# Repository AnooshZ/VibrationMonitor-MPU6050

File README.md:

# 📈 Vibration Monitoring System | Arduino → STM32 Custom PCB

A real-time vibration monitoring system built around the **MPU6050 accelerometer**, originally developed using an Arduino UNO and Python, and subsequently redesigned around an **STM32F103 microcontroller on a custom-designed PCB**.

The project explores embedded systems, sensor interfacing, digital signal processing, PCB design, and hardware debugging.

The original Arduino prototype successfully demonstrated vibration detection, signal filtering, threshold-based LED indication, and real-time Python visualization. The STM32 redesign aims to improve sampling consistency, timing control, and overall system flexibility while providing practical experience developing and validating custom embedded hardware.

**Current Status: Custom PCB manufactured, assembled, powered, and successfully programmed. Hardware bring-up completed; STM32 firmware development in progress.**

---

## 🎯 Project Overview

The project began as an experiment in vibration analysis using an Arduino UNO and MPU6050 accelerometer.

The initial implementation acquired accelerometer measurements, processed vibration data, applied filtering, and communicated results to a Python application for real-time visualization and data logging.

Although the prototype worked, I encountered limitations involving sampling consistency, timing accuracy, and flexibility in controlling the underlying hardware.

To address these limitations, I redesigned the system around an STM32F103C8T6 microcontroller and developed my first custom PCB using KiCad.

A major objective throughout this redesign was to learn directly from technical documentation rather than relying heavily on tutorials. This involved studying component datasheets, application notes, and the STM32 reference manual to understand peripheral configuration, clock circuitry, power distribution, communication interfaces, and PCB layout.

---

## 🚀 Project Development Status

| Stage | Status |
|---|---|
| Arduino + MPU6050 prototype | ✅ Complete |
| Vibration detection and filtering | ✅ Complete on Arduino |
| Python visualization and CSV logging | ✅ Complete on Arduino |
| STM32 schematic design | ✅ Complete |
| Custom PCB layout and design-rule verification | ✅ Complete |
| PCB manufacturing and assembly | ✅ Complete |
| Power rail verification | ✅ Complete |
| SWD communication and MCU identification | ✅ Complete |
| STM32 programming and debugging | ✅ Complete |
| Bare-metal GPIO configuration and LED blinking | ✅ Complete |
| External MPU6050 integration | 🔄 Upcoming |
| STM32 I²C firmware | 🔄 Upcoming |
| STM32 vibration acquisition and processing | 🔄 Planned |
| STM32-to-Python communication | 🔄 Planned |
| Physical board demonstration videos | 🔄 Coming soon |

---

## 🧠 Original Arduino Prototype

The first version of the system was developed using an Arduino UNO, MPU6050 sensor module, and Python.

### Features

- Real-time vibration measurements using the MPU6050 three-axis accelerometer
- High-pass filtering to reduce unwanted low-frequency components
- RMS smoothing for more stable vibration measurements
- Threshold-based LED indication
- Serial communication between Arduino and Python
- Real-time plotting of vibration magnitude and RMS values
- Timestamped CSV logging for further analysis
- Initial experimentation with FFT-based vibration analysis

### Hardware

- Arduino UNO
- MPU6050 accelerometer module
- Breadboard and jumper wires
- LED with current-limiting resistor
- USB connection for serial communication

### Arduino Connections

| Arduino Pin | Connection |
|---|---|
| 5V | MPU6050 module VCC |
| GND | MPU6050 GND |
| A4 | MPU6050 SDA |
| A5 | MPU6050 SCL |
| D8 | LED output |

### Software

**Arduino:** Acquires acceleration measurements, performs vibration-related calculations, applies filtering, and activates the LED when the configured vibration threshold is exceeded.

**Python:** Receives serial measurements, plots vibration magnitude and RMS values in real time, and saves measurement data for later analysis.

### Original Prototype Demonstration

[Watch the Arduino vibration monitoring demo](Demo/VibrationsMonitorDemo.mp4)

The demonstration uses a massage gun to introduce controlled vibrations at different intensity levels.

At lower vibration levels, the LED remains off. At higher vibration levels, the measured vibration exceeds the threshold and activates the LED.

The Python visualization displays the corresponding changes in vibration magnitude and RMS measurements.

---

## 🔧 STM32 Custom PCB Redesign

The second iteration replaces the Arduino development board with a custom PCB designed around the **STM32F103C8T6 ARM Cortex-M3 microcontroller**.

This redesign provides greater control over the hardware and creates a foundation for implementing more consistent sampling, hardware timers, sensor communication, and embedded signal processing.

### Hardware Features

| Component / Interface | Purpose |
|---|---|
| STM32F103C8T6 | Main ARM Cortex-M3 microcontroller |
| TPS7A2033 LDO | Regulated 3.3V power supply |
| 8 MHz external crystal | External clock source |
| USB Micro-B connector | USB connectivity and power input |
| USB ESD protection | Protection for USB data lines |
| SWD header | Programming and hardware debugging |
| UART header | Serial communication and debugging |
| I²C header | External MPU6050 sensor connection |
| Analog supply filtering | Filtering for the MCU analog power domain |
| BOOT0 selection switch | Boot mode configuration |
| Reset circuitry | MCU reset control |
| Status LEDs | Power indication and firmware-controlled output |

### Power Distribution

The PCB uses a dedicated 3.3V low-dropout regulator to supply the STM32 and associated circuitry.

The design includes local decoupling capacitors near the microcontroller power pins, bulk capacitance for supply stability, and filtering for the analog supply domain.

### Clock Circuitry

An 8 MHz external crystal and its supporting capacitors are included to provide an external clock option.

The STM32 can also operate using its internal oscillator, allowing firmware development and initial bring-up without requiring the external crystal to be configured.

### Programming and Debugging

A dedicated SWD header exposes the STM32 programming and debugging signals.

Using an ST-Link programmer and STM32CubeIDE, the microcontroller can be programmed, halted, inspected, and debugged directly on the custom PCB.

### Sensor Interface

The PCB includes an I²C header for connecting an external MPU6050 module.

This allows the sensor interface to be developed and tested independently before integrating vibration processing into the STM32 firmware.

---

## 🛠️ PCB Design and Manufacturing

The schematic and PCB layout were developed in **KiCad**.

The design process involved:

- Studying STM32 datasheets and reference documentation
- Selecting components and verifying footprints
- Designing the power distribution and decoupling networks
- Implementing clock, reset, boot, USB, and debugging circuitry
- Routing a two-layer PCB
- Considering return paths, trace routing, and placement of decoupling components
- Running electrical rule checks (ERC) and design rule checks (DRC)
- Preparing manufacturing files and a bill of materials
- Ordering and assembling the physical PCB

The boards were manufactured through **JLCPCB**, with additional manual soldering and hardware bring-up performed after delivery.

### PCB Design Files

The KiCad project files are available in the [`KiCad/`](KiCad/) directory.

These include:

- `.kicad_pro` — KiCad project configuration
- `.kicad_sch` — Complete electrical schematic
- `.kicad_pcb` — PCB layout and routing

The directory also contains PCB renders and schematic images for convenient viewing without KiCad.

---

## ⚡ Hardware Bring-Up and Validation

After receiving the manufactured PCB, I began testing the board before developing the full application firmware.

### Power Verification

Using a digital multimeter, I verified the board's power connections and regulated 3.3V supply.

The onboard power indicator LED also confirmed the presence of the regulated supply.

### SWD and Microcontroller Verification

Using an ST-Link programmer and STM32CubeProgrammer, I successfully established communication with the STM32F103.

The debugger identified the target microcontroller and was able to access its internal flash memory.

This confirmed that the microcontroller was powered, responsive, and accessible through the custom SWD interface.

### Hardware Debugging

During initial bring-up, the debugger could not establish communication with the microcontroller.

Investigation of the reset circuitry revealed an issue with the physical reset pushbutton footprint and its pin mapping, which caused the NRST signal to remain asserted.

After identifying and removing the problematic switch, SWD communication was successfully restored.

This was a valuable practical lesson in component footprint verification, PCB assembly, and systematic hardware fault isolation.

The board can currently be reset through the debugging interface or by power cycling.

### First Successful Firmware Test

After confirming SWD communication, I created a bare-metal STM32 project in STM32CubeIDE.

Rather than relying on automatically generated GPIO initialization code, I configured the necessary registers directly using the STM32 reference manual.

This involved:

- Enabling the GPIOC peripheral clock through the RCC register
- Configuring PC13 as a general-purpose output
- Accessing memory-mapped peripheral registers using C pointers
- Using bitwise operations to configure and control GPIO
- Implementing a software delay loop
- Flashing and executing the program through ST-Link

**Result: The onboard LED successfully blinks under firmware control.**

This verified the complete development path from writing and compiling firmware to programming and executing code on the custom STM32 PCB.

---

## 💻 STM32 Firmware Development

The STM32 firmware is currently under active development.

The initial milestone was establishing reliable programming and GPIO control, which has now been achieved.

The next stage is integrating the MPU6050 accelerometer through the external I²C header.

### Planned Firmware Milestones

1. Configure STM32 I²C communication.
2. Detect and initialize the MPU6050.
3. Read raw three-axis acceleration measurements.
4. Implement consistent sensor sampling using hardware timers.
5. Process acceleration measurements to calculate vibration magnitude and RMS values.
6. Reimplement threshold-based vibration detection.
7. Transmit measurements to a host computer for Python visualization.
8. Investigate FFT-based frequency-domain vibration analysis.

The objective is to progressively replace the functionality of the original Arduino prototype with firmware developed specifically for the STM32 platform.

### Development Approach

I am currently focusing on register-level programming to develop a deeper understanding of the STM32 peripherals, memory-mapped I/O, peripheral clock control, and embedded C.

This approach provides direct experience with the underlying microcontroller hardware before introducing higher-level abstraction libraries where appropriate.

---

## 📹 Physical PCB Demonstrations — Coming Soon

The custom PCB has completed its initial hardware bring-up, and the STM32 has been successfully programmed and tested with a blinking LED.

I am currently working on the firmware and preparing to integrate the external MPU6050 sensor.

**Videos demonstrating the physical PCB, successful firmware execution, sensor communication, and eventually real-time vibration monitoring will be uploaded as development progresses.**

These demonstrations will document the transition from the original Arduino prototype to the working custom STM32-based system.

---

## 📁 Repository Structure

```text
VibrationMonitor-MPU6050/
│
├── Arduino/
│   └── Original Arduino prototype firmware
│
├── Python/
│   └── Real-time plotting and data logging
│
├── KiCad/
│   ├── STM32_Vibrations_Monitor.kicad_pro
│   ├── STM32_Vibrations_Monitor.kicad_sch
│   ├── STM32_Vibrations_Monitor.kicad_pcb
│   └── KiCad Images/
│       ├── PCB_3D_Top_View.jpeg
│       ├── PCB_3D_Bottom_View.jpeg
│       ├── PCB_Design.jpeg
│       └── Schematic.jpeg
│
├── Demo/
│   └── Original Arduino demonstration
│
├── LICENSE
└── README.md
```

*STM32 firmware files and physical PCB demonstrations will be added as development continues.*

---

## 🧰 Tools and Technologies

**Hardware and PCB Design**
- KiCad
- STM32F103C8T6
- MPU6050 accelerometer
- JLCPCB manufacturing and assembly
- Digital multimeter and soldering equipment

**Embedded Development**
- Embedded C
- STM32CubeIDE
- STM32CubeProgrammer
- ST-Link / SWD
- Register-level peripheral configuration
- I²C, UART, and GPIO

**Software and Data Processing**
- Arduino IDE
- Python 3
- Matplotlib
- PySerial
- Digital filtering and RMS calculations
- FFT-based signal analysis

**Documentation and Version Control**
- GitHub
- STM32 reference manual and datasheets
- Component datasheets and application notes

---

## 📚 Key Learning Outcomes

This project has provided practical experience across both hardware and firmware development.

Some of the most valuable learning experiences have included:

- Designing a complete STM32-based embedded PCB from component documentation
- Understanding microcontroller power, reset, clock, and boot requirements
- Developing and verifying a PCB layout for manufacturing
- Performing first-time hardware bring-up and electrical measurements
- Diagnosing a physical PCB assembly and footprint issue
- Establishing reliable SWD communication
- Programming a custom STM32 board using ST-Link
- Writing bare-metal C firmware using memory-mapped peripheral registers
- Connecting hardware design decisions with actual firmware behavior

The next objective is to bring the complete vibration monitoring application onto the STM32 platform.

---

## 👨‍💻 Author

**Anoosh Zaidi**  
Computer Engineering Student  
Toronto Metropolitan University

This project is part of my ongoing exploration of embedded systems, PCB design, hardware debugging, and firmware development.

---

## 📜 License

This project is released under the MIT License. See [LICENSE](LICENSE) for details.

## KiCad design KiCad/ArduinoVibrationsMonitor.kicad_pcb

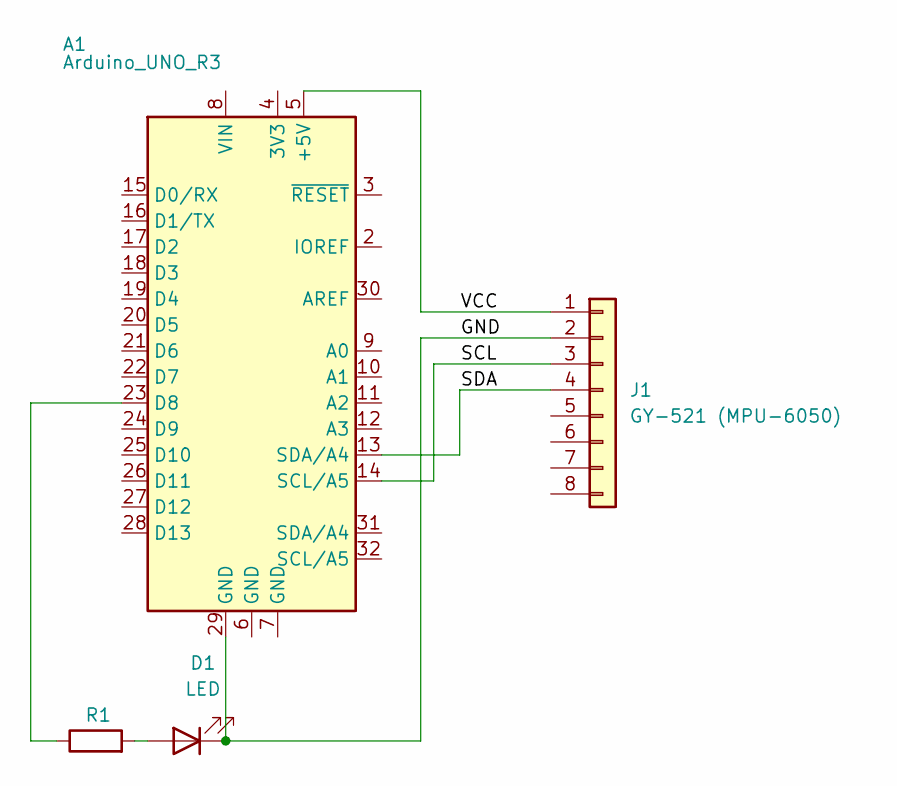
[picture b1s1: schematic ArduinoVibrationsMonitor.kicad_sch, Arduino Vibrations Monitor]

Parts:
A1: Arduino_UNO_R3
D1: LED; R_0805_2012Metric
J1: GY-521 (MPU-6050); PinHeader_1x08_P2.54mm_Vertical
R1: 220R; R_0805_2012Metric

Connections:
/GND: A1.29 (GND), D1.1 (K), J1.2
/SCL: A1.14 (SCL/A5), J1.3
/SDA: A1.13 (SDA/A4), J1.4
/VCC: A1.5 (+5V), J1.1
unnamed: A1.23 (D8), R1.1
unnamed: D1.2 (A), R1.2

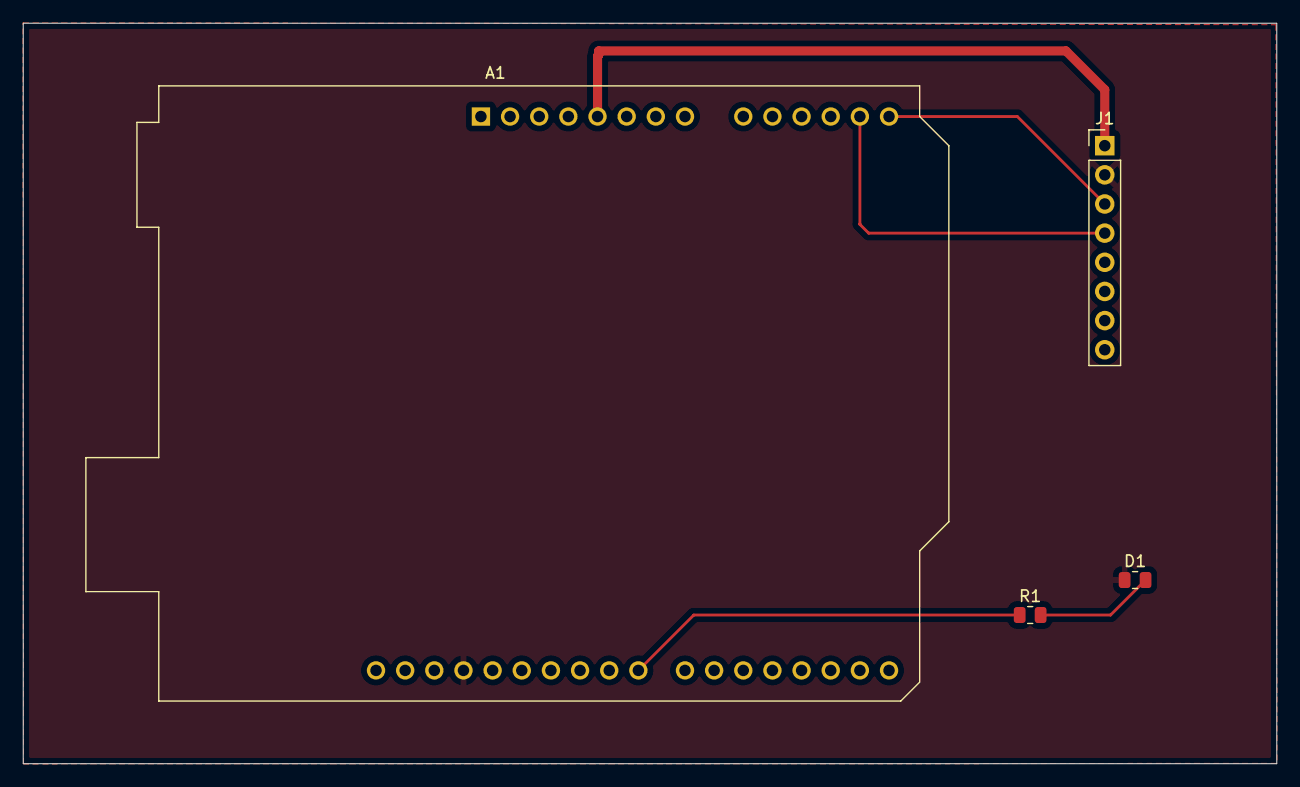
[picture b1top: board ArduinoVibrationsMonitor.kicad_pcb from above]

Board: 2 copper layers, 109.2 x 64.5 mm, 4 parts (0 on the bottom side), 6 nets.

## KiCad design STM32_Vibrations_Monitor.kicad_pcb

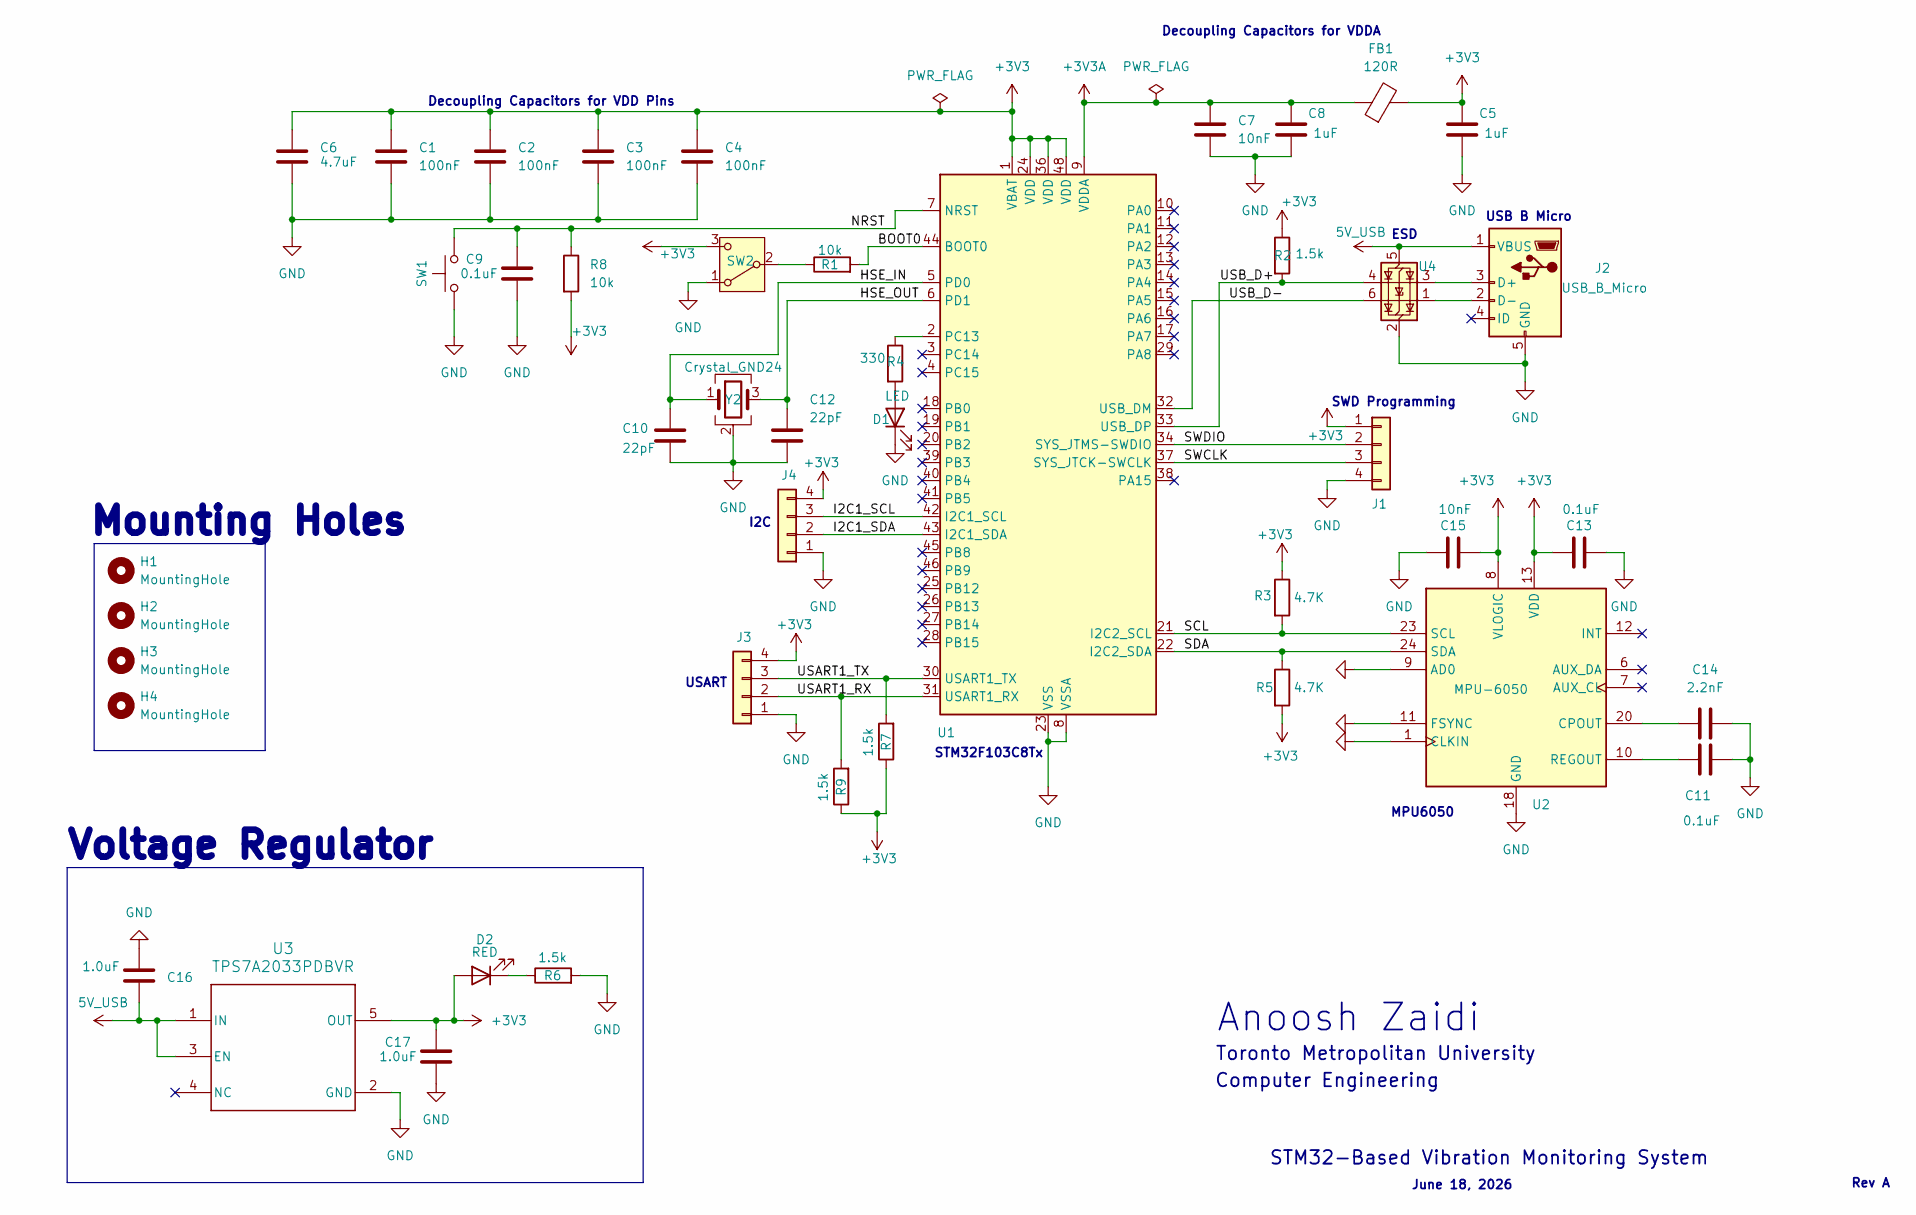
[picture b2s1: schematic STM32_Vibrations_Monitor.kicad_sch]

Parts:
C1, C2, C3, C4: 100nF; C_0603_1608Metric
C5, C8: 1uF; C_0805_2012Metric
C6: 4.7uF; C_0805_2012Metric
C7, C15: 10nF; C_0603_1608Metric
C9, C11, C13: 0.1uF; C_0603_1608Metric
C10, C12: 22pF; C_0603_1608Metric
C14: 2.2nF; C_0603_1608Metric
C16, C17: 1.0uF; C_0805_2012Metric
D1: LED; LED_0603_1608Metric
D2: RED; LED_0603_1608Metric
FB1: 120R; L_0603_1608Metric
H1, H2, H3, H4: MountingHole; MountingHole_2.2mm_M2
J1, J3, J4: Conn_01x04; PinHeader_1x04_P2.54mm_Vertical
J2: USB_B_Micro; USB_Micro-B_Molex-105017-0001
R1, R8: 10k; R_0603_1608Metric
R2, R6, R7, R9: 1.5k; R_0603_1608Metric
R3, R5: 4.7K; R_0603_1608Metric
R4: 330; R_0603_1608Metric
SW1: SW_Push; SMT_FS
SW2: SW_SPDT; SWITCH_1SCQN
U1: STM32F103C8Tx; LQFP-48_7x7mm_P0.5mm
U2: MPU-6050; InvenSense_QFN-24_4x4mm_P0.5mm
U3: TPS7A2033PDBVR; DBV0005A-MFG
U4: USBLC6-2SC6; SOT-23-6
Y2: Crystal_GND24; Crystal_SMD_Abracon_ABM3B-4Pin_5.0x3.2mm

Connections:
5V_USB: C16.1, J2.1 (VBUS), U3.1 (IN), U3.3 (EN), U4.5 (VBUS)
+3V3: C1.1, C2.1, C3.1, C4.1, C5.1, C6.1, C13.1, C15.2, C17.1, D2.2 (A), FB1.2, J1.1, J3.4, J4.4, R2.1, R3.1, R5.2, R7.1, R8.2, R9.1, SW2.3 (C), U1.1 (VBAT), U1.24 (VDD), U1.36 (VDD), U1.48 (VDD), U2.8 (VLOGIC), U2.13 (VDD), U3.5 (OUT)
+3V3A: C7.1, C8.1, FB1.1, U1.9 (VDDA)
/BOOT0: R1.2, U1.44 (BOOT0)
/HSE_IN: C10.1, U1.5 (PD0), Y2.1
/HSE_OUT: C12.1, U1.6 (PD1), Y2.3
/I2C1_SCL: J4.3, U1.42 (I2C1_SCL)
/I2C1_SDA: J4.2, U1.43 (I2C1_SDA)
/NRST: C9.1, R8.1, SW1.2, U1.7 (NRST)
/SCL: R3.2, U1.21 (I2C2_SCL), U2.23 (SCL)
/SDA: R5.1, U1.22 (I2C2_SDA), U2.24 (SDA)
/SWCLK: J1.3, U1.37 (SYS_JTCK-SWCLK)
/SWDIO: J1.2, U1.34 (SYS_JTMS-SWDIO)
/USART1_RX: J3.2, R9.2, U1.31 (USART1_RX)
/USART1_TX: J3.3, R7.2, U1.30 (USART1_TX)
/USB_D+: R2.2, U1.33 (USB_DP), U4.4 (I/O2)
/USB_D-: U1.32 (USB_DM), U4.6 (I/O1)
GND: C1.2, C2.2, C3.2, C4.2, C5.2, C6.2, C7.2, C8.2, C9.2, C10.2, C11.2, C12.2, C13.2, C14.2, C15.1, C16.2, C17.2, D1.1 (K), J1.4, J2.5 (GND), J3.1, J4.1, R6.2, SW1.1, SW2.1 (A), U1.8 (VSSA), U1.23 (VSS), U1.35 (VSS), U1.47 (VSS), U2.1 (CLKIN), U2.9 (AD0), U2.11 (FSYNC), U2.18 (GND), U3.2 (GND), U4.2 (GND), Y2.2 (G), Y2.4 (G)
unnamed: D1.2 (A), R4.2
unnamed: D2.1 (K), R6.1
unnamed: J2.3 (D+), U4.3 (I/O2)
unnamed: J2.2 (D-), U4.1 (I/O1)
unnamed: R1.1, SW2.2 (B)
unnamed: R4.1, U1.2 (PC13)
unnamed: C14.1, U2.20 (CPOUT)
unnamed: C11.1, U2.10 (REGOUT)

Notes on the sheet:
Decoupling Capacitors for VDDA
Rev A
Computer Engineering
Decoupling Capacitors for VDD Pins
I2C
MPU6050
Mounting Holes
STM32F103C8Tx
STM32-Based Vibration Monitoring System
SWD Programming
Anoosh Zaidi
Voltage Regulator
Toronto Metropolitan University
June 18, 2026
ESD
USB B Micro
USART

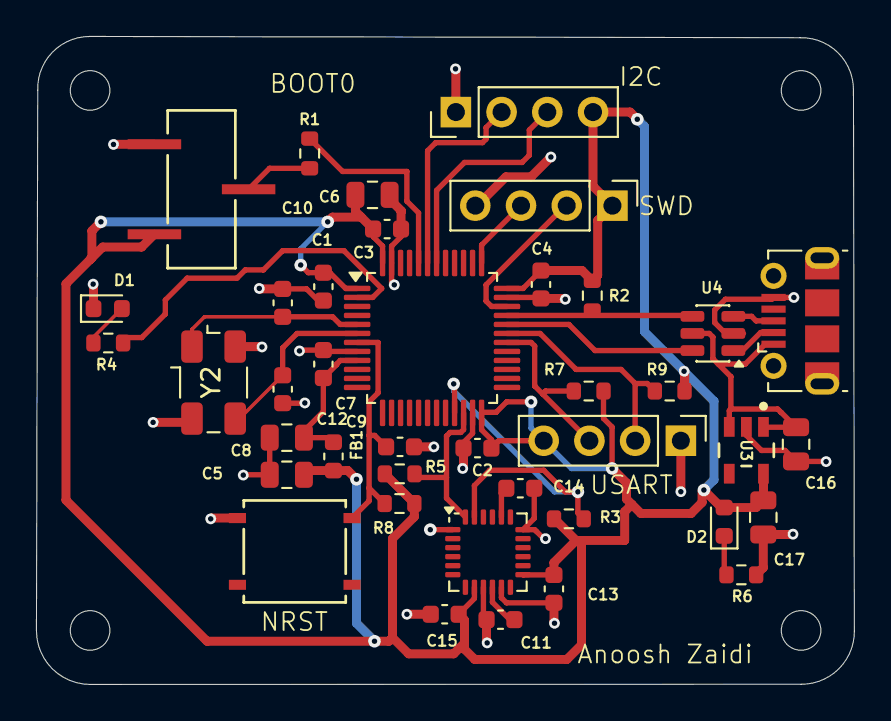
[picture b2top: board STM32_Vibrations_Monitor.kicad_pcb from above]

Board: 2 copper layers, 45.4 x 36.0 mm, 44 parts (0 on the bottom side), 26 nets.

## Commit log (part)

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2025-09-30 Add Arduino vibration monitor sketch
2025-09-30 Add Python live plotting script
2025-10-08 Added KiCad schematic and PCB layout
2025-10-08 Added PCB renders (3D, Top, Silkscreen, Schematic)
2025-10-08 Add project demo video
    - The massage gun at level 1 generates minor vibrations, the graph spikes slightly, but the LED stays off (below threshold).
    - When increased to level 6, the vibrations cross the defined threshold, triggering the LED indicator and showing large amplitude spikes in the live Python plot.
    - The setup demonstrates the system’s real-time vibration detection and threshold-based response.
